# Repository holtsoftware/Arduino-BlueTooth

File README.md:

Arduino-BlueTooth
=================

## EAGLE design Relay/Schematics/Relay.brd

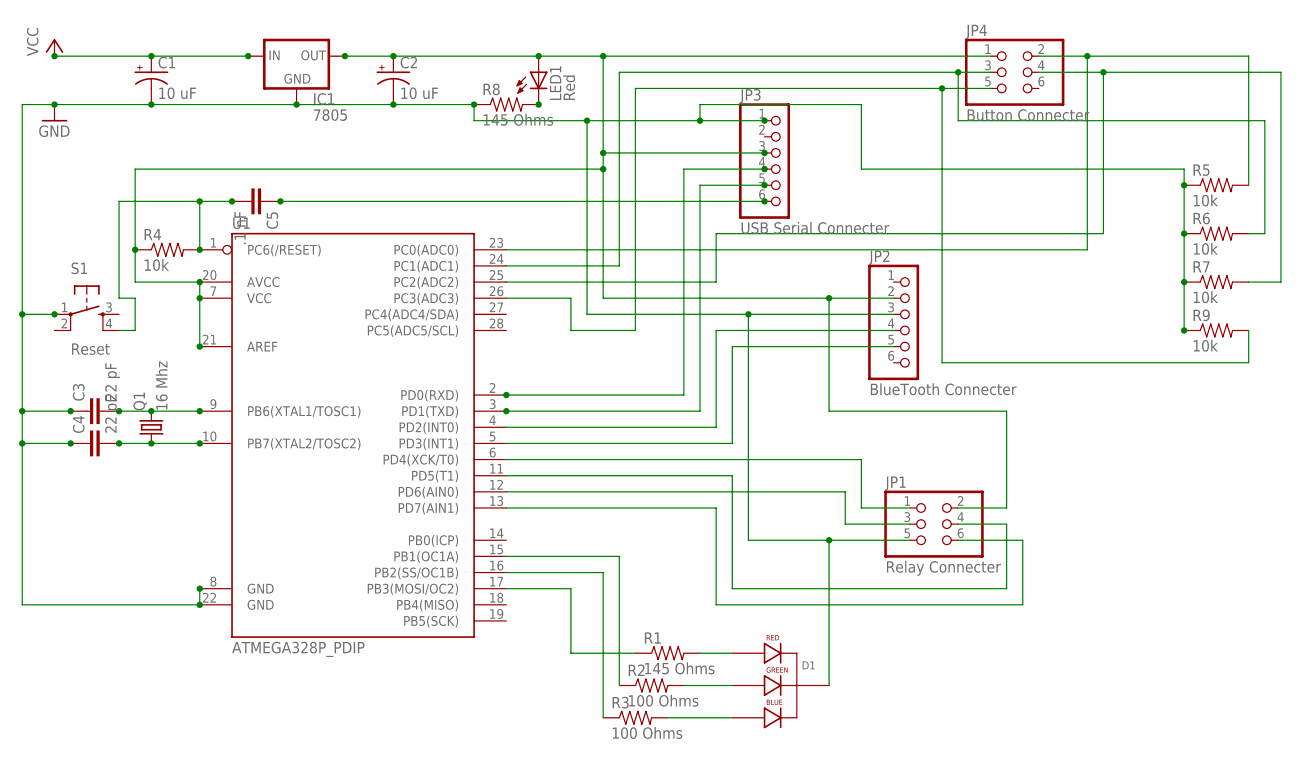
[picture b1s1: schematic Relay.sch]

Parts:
C1, C2: 10 uF; CPOL-RADIAL-10UF-25V
C3, C4: 22 pF; CAP-PTH-SMALL2
C5: .1 nF; CAP-PTH-SMALL2
D1: LED-RGB-CC-THRUCLEAR; LED-RGB-THRU
IC1: 7805; 78XXS
JP1: Relay Connecter; 2X03
JP2: BlueTooth Connecter; 1X06
JP3: USB Serial Connecter; 1X06
JP4: Button Connecter; 2X03
LED1: Red; LED3MM
Q1: 16 Mhz; HC49/S
R1, R8: 145 Ohms; AXIAL-0.4
R2, R3: 100 Ohms; AXIAL-0.4
R4, R5, R6, R7, R9: 10k; 0402-RES
S1: Reset; TACTILE-PTH
U1: ATMEGA328P_PDIP; DIL28-3

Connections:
GND: C1.2 (-), C2.2 (-), C3.1, C4.1, D1.2 (CATHODE), IC1.GND, JP1.5, JP2.3, JP3.1, R5.1, R6.1, R7.1, R8.P$1 (1), R9.1, S1.1, U1.8 (GND), U1.22 (GND)
unnamed: C2.1 (+), IC1.OUT, JP1.2, JP2.2, JP3.3, JP4.1, LED1.A, R4.1, U1.7 (VCC), U1.20 (AVCC), U1.21 (AREF)
unnamed: LED1.K (C), R8.P$2 (2)
unnamed: C5.2, R4.2, S1.4, U1.1 (PC6(/RESET))
unnamed: C3.2, Q1.2, U1.9 (PB6(XTAL1/TOSC1))
unnamed: C4.2, Q1.1, U1.10 (PB7(XTAL2/TOSC2))
unnamed: JP3.4, U1.2 (PD0(RXD))
unnamed: JP3.5, U1.3 (PD1(TXD))
unnamed: JP2.4, U1.4 (PD2(INT0))
unnamed: JP2.5, U1.5 (PD3(INT1))
unnamed: JP1.1, U1.6 (PD4(XCK/T0))
unnamed: JP1.4, U1.11 (PD5(T1))
unnamed: JP1.3, U1.12 (PD6(AIN0))
unnamed: JP1.6, U1.13 (PD7(AIN1))
unnamed: D1.1 (RED_CATHODE), R1.P$2 (2)
unnamed: D1.3 (GREEN_CATHODE), R2.P$2 (2)
unnamed: D1.4 (BLUE_CATHODE), R3.P$2 (2)
unnamed: R1.P$1 (1), U1.17 (PB3(MOSI/OC2))
unnamed: R2.P$1 (1), U1.15 (PB1(OC1A))
unnamed: R3.P$1 (1), U1.16 (PB2(SS/OC1B))
unnamed: JP4.2, R5.2, U1.23 (PC0(ADC0))
unnamed: JP4.3, R6.2, U1.24 (PC1(ADC1))
unnamed: JP4.4, R7.2, U1.25 (PC2(ADC2))
unnamed: JP4.5, R9.2, U1.26 (PC3(ADC3))
unnamed: C5.1, JP3.6
VCC: C1.1 (+), IC1.IN

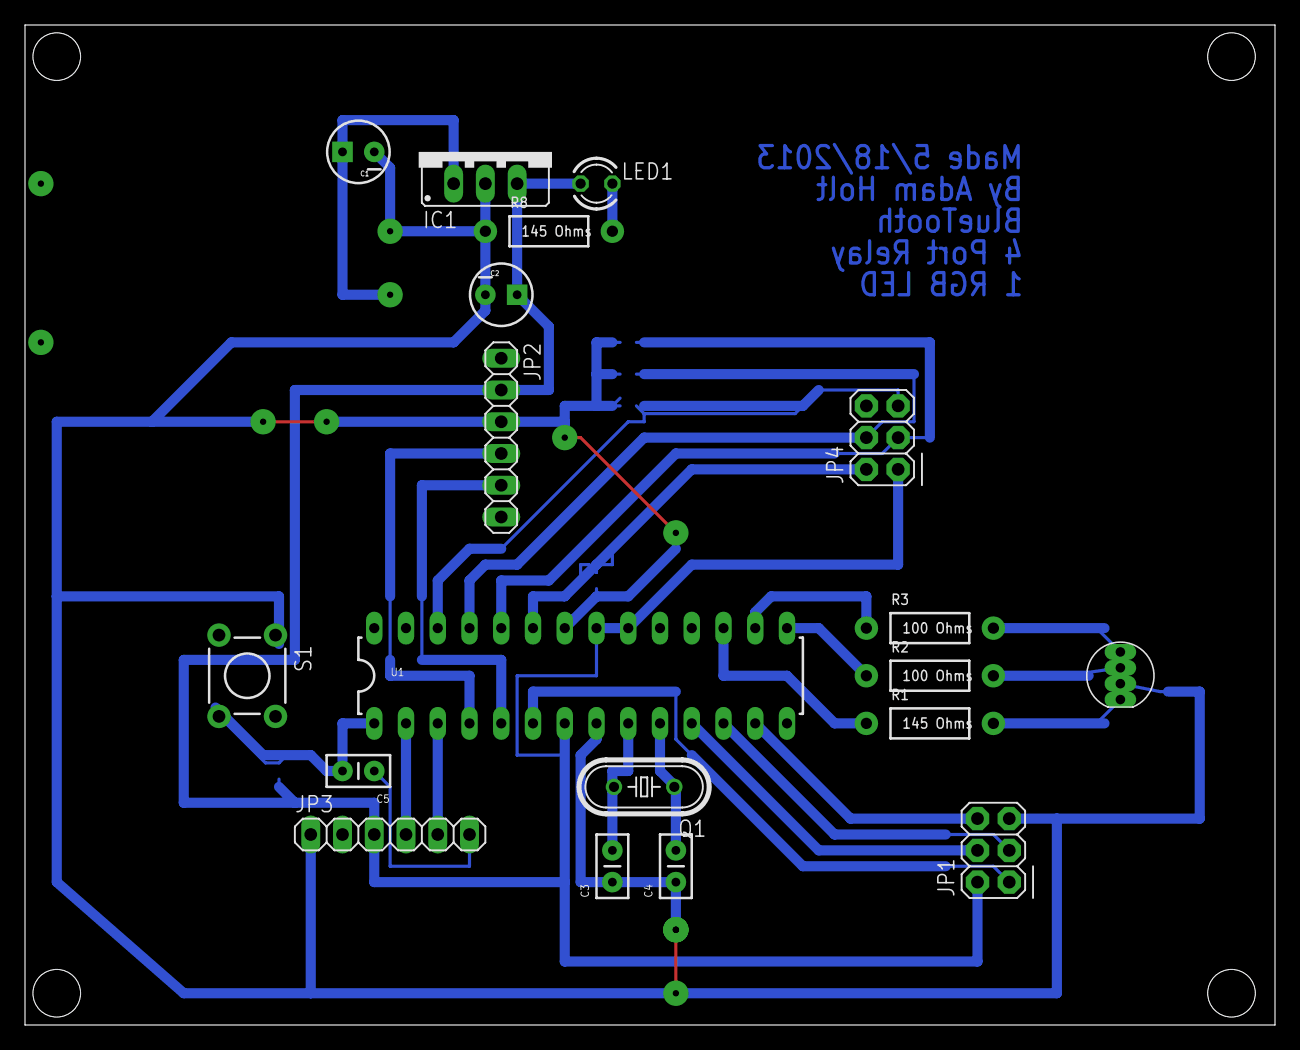
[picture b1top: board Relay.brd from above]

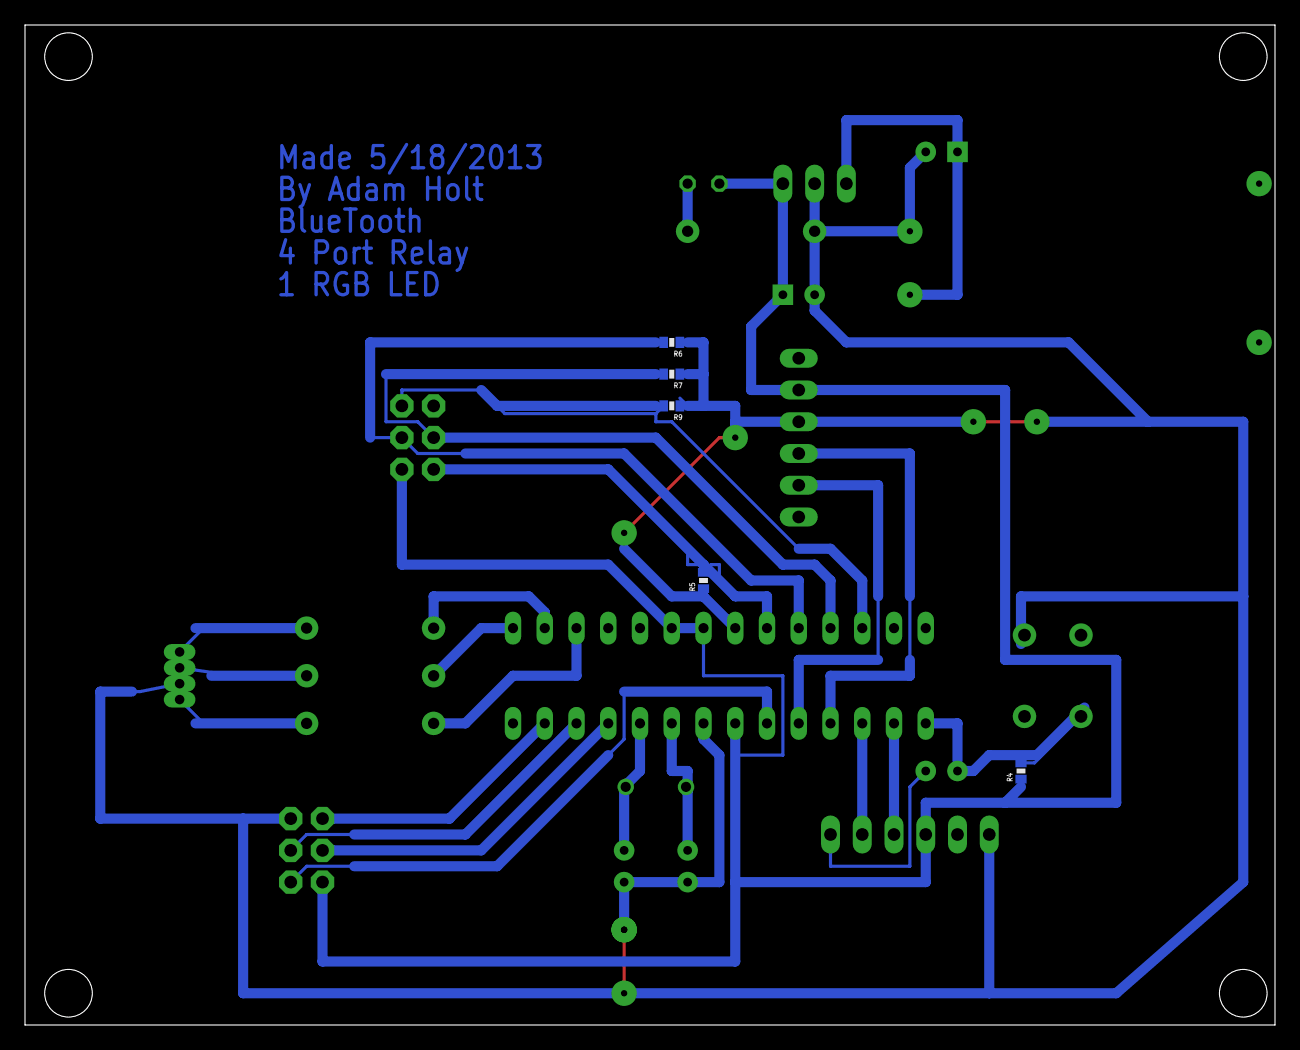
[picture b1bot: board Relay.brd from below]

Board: 2 copper layers, 100.0 x 80.0 mm, 24 parts (5 on the bottom side), 26 nets.

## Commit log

2013-05-18 Check in of first bluetooth test
2013-05-21 Added the Four Port Relay project.
2013-05-21 Added the CommandProcesser and CommandArgs class.
2013-05-23 Removed backup Eagle Files. More Progress on the Arduino side of the Relay project. Updated .gitignore to ignore Eagle Backup files.
2013-05-27 Added types names to match the .NET Framework added a BitConverter class
2013-05-27 More Progress
2013-05-28 Fixed a bug on the board where the led was not wired up to a pwn pin.
2013-05-28 Added some Serial logging for testing. Assigned the correct pins to Relay.
2013-06-03 Started Building the Windows Phone app. During this process created a packet style of sending across the serial connection.
2013-06-05 Wired up the view models to ControlPage.xaml. Need to update the arduino code before I can test this update.
2013-06-06 Started Updating the Arduino code with namespaces that match the wp app, and use the packet with serial.
2013-06-06 Missed some files with last commit.
2013-06-08 Finish coding the Processer class and wiring up all object. Time for testing.
2013-06-08 fixed bugs found while testing
2013-06-11 Removed a delay that was left over from debugging.
2013-06-12 Implemented the Buttons class. Updated relay class to send packets when Set_Relay* is called. Updated main class to call the button class and give the button class the relay class refrence.
2013-06-12 Updated App icon. Added some logic so when you go back the main page does not auto connect.
2013-06-13 Added in app voice command. Added color drop down

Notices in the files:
parts and their libraries:
SparkFun-Capacitors: Licensing: CC v3.0 Share-Alike You are welcome to use this library for commercial purposes.
